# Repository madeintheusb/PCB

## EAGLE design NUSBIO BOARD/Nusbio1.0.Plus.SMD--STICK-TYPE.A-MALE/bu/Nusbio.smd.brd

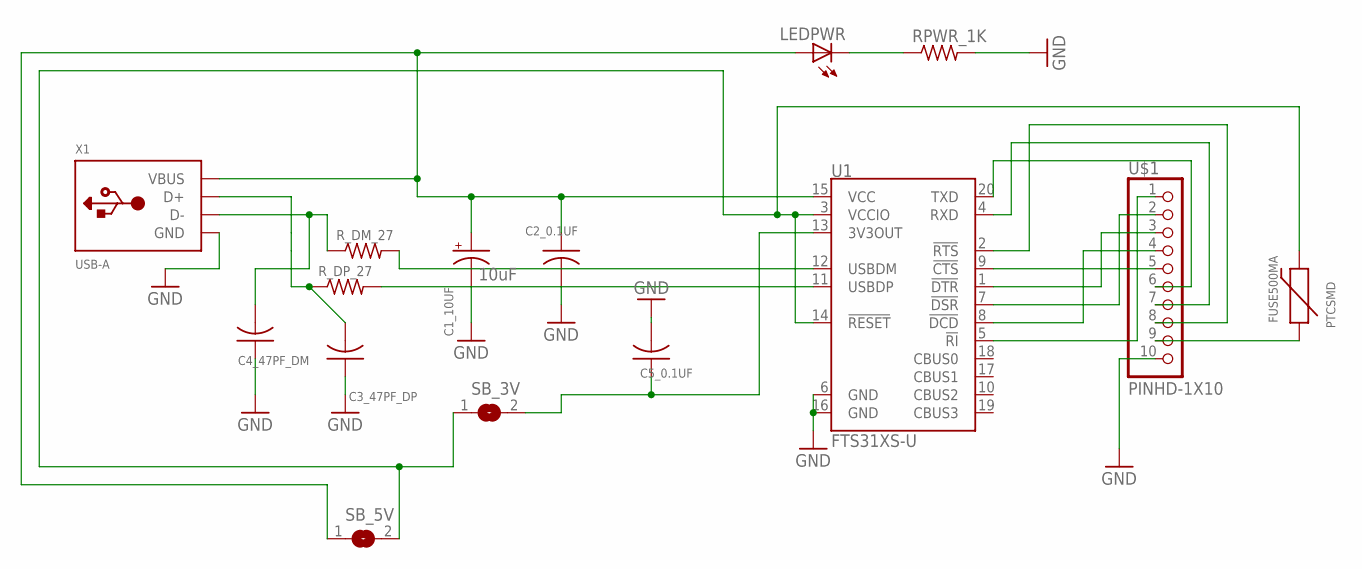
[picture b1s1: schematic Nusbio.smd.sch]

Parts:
C1_10UF: 10uF; EIA3216
C2_0.1UF, C3_47PF_DP, C4_47PF_DM, C5_0.1UF: C-USC1206; C1206
FUSE500MA: PTCSMD; PTC-1206
LEDPWR: LEDCHIPLED_0805; CHIPLED_0805
RPWR_1K: R-US_R0805; R0805
R_DM_27: R-US_R0805; R0805
R_DP_27: R-US_R0805; R0805
SB_3V, SB_5V: SOLDERJUMPERREFLOW; SOLDERJUMPER_REFLOW
U1: FTS31XS-U; SSOP20_L
U$1: PINHD-1X10; 1X10-BIG
X1: USB-A; MOLEX_480371000

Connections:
GND: C1_10UF.C (-), C2_0.1UF.2, C3_47PF_DP.1, C4_47PF_DM.1, C5_0.1UF.2, RPWR_1K.2, U1.6 (GND), U1.16 (GND), U$1.10, X1.4 (GND)
unnamed: FUSE500MA.1, U$1.9
unnamed: C5_0.1UF.1, SB_3V.2, U1.13 (3V3OUT)
unnamed: LEDPWR.C, RPWR_1K.1
unnamed: R_DM_27.2, U1.12 (USBDM)
unnamed: R_DP_27.2, U1.11 (USBDP)
unnamed: U1.20 (TXD), U$1.6
unnamed: U1.7 (!DSR), U$1.2
unnamed: U1.5 (!RI), U$1.1
unnamed: U1.1 (!DTR), U$1.3
unnamed: U1.8 (!DCD), U$1.4
unnamed: U1.9 (!CTS), U$1.5
unnamed: U1.4 (RXD), U$1.7
unnamed: U1.2 (!RTS), U$1.8
unnamed: FUSE500MA.2, SB_3V.1, SB_5V.2, U1.3 (VCCIO), U1.14 (!RESET)
unnamed: C3_47PF_DP.2, R_DP_27.1, X1.3 (D+)
unnamed: C4_47PF_DM.2, R_DM_27.1, X1.2 (D-)
unnamed: C1_10UF.A (+), C2_0.1UF.1, LEDPWR.A, SB_5V.1, U1.15 (VCC), X1.1 (VBUS)

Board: 2 copper layers, 15 parts (0 on the bottom side), 18 nets, no tracks yet.

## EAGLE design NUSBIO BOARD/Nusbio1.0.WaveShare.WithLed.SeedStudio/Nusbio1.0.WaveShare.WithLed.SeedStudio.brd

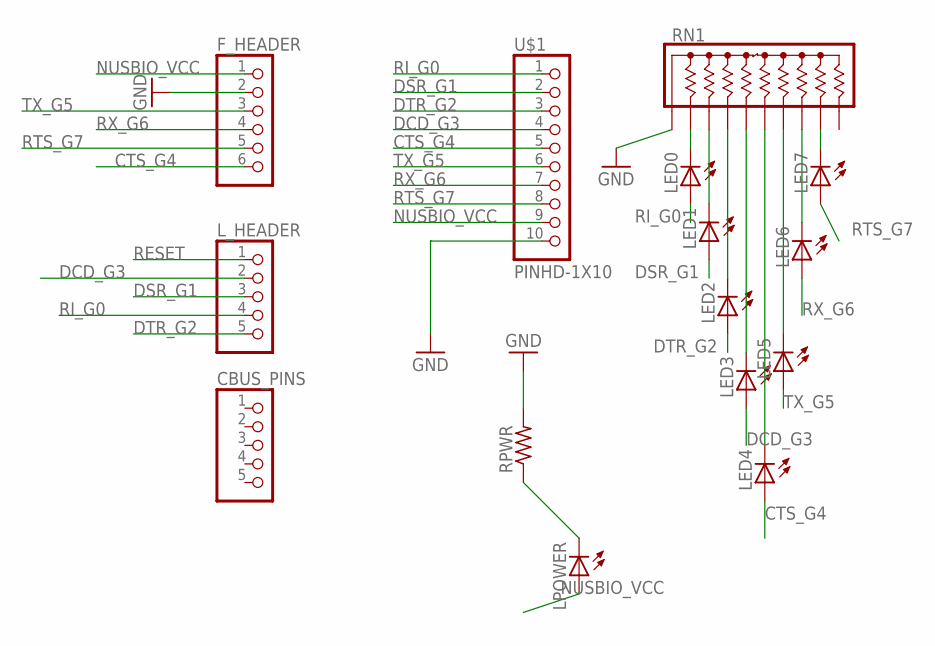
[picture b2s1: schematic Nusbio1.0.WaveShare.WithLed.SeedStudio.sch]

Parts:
CBUS_PINS: PINHD-1X5; 1X05
F_HEADER: PINHD-1X6; 1X06
LED0, LED1, LED2, LED3, LED4, LED5, LED6, LED7: LEDSMT1206; 1206
LPOWER: LEDSMT1206; 1206
L_HEADER: PINHD-1X5; 1X05
RN1: 4610X; SIP10
RPWR: R-US_R1206; R1206
U$1: PINHD-1X10; 1X10-BIG

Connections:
CTS_G4: F_HEADER.6, LED4.A, U$1.5
DCD_G3: LED3.A, L_HEADER.2, U$1.4
DSR_G1: LED1.A, L_HEADER.3, U$1.2
DTR_G2: LED2.A, L_HEADER.5, U$1.3
GND: F_HEADER.2, RN1.1, RPWR.2, U$1.10; also elsewhere on the board
unnamed: LED1.C, RN1.3
unnamed: LED0.C, RN1.2
unnamed: LED2.C, RN1.4
unnamed: LED3.C, RN1.5
unnamed: LED4.C, RN1.6
unnamed: LED7.C, RN1.9
unnamed: LED5.C, RN1.7
unnamed: LED6.C, RN1.8
unnamed 13: LPOWER.C, RPWR.1; also elsewhere on the board
NUSBIO_VCC: F_HEADER.1, LPOWER.A, U$1.9
RESET: L_HEADER.1
RI_G0: LED0.A, L_HEADER.4, U$1.1
RTS_G7: F_HEADER.5, LED7.A, U$1.8
RX_G6: F_HEADER.4, LED6.A, U$1.7
TX_G5: F_HEADER.3, LED5.A, U$1.6

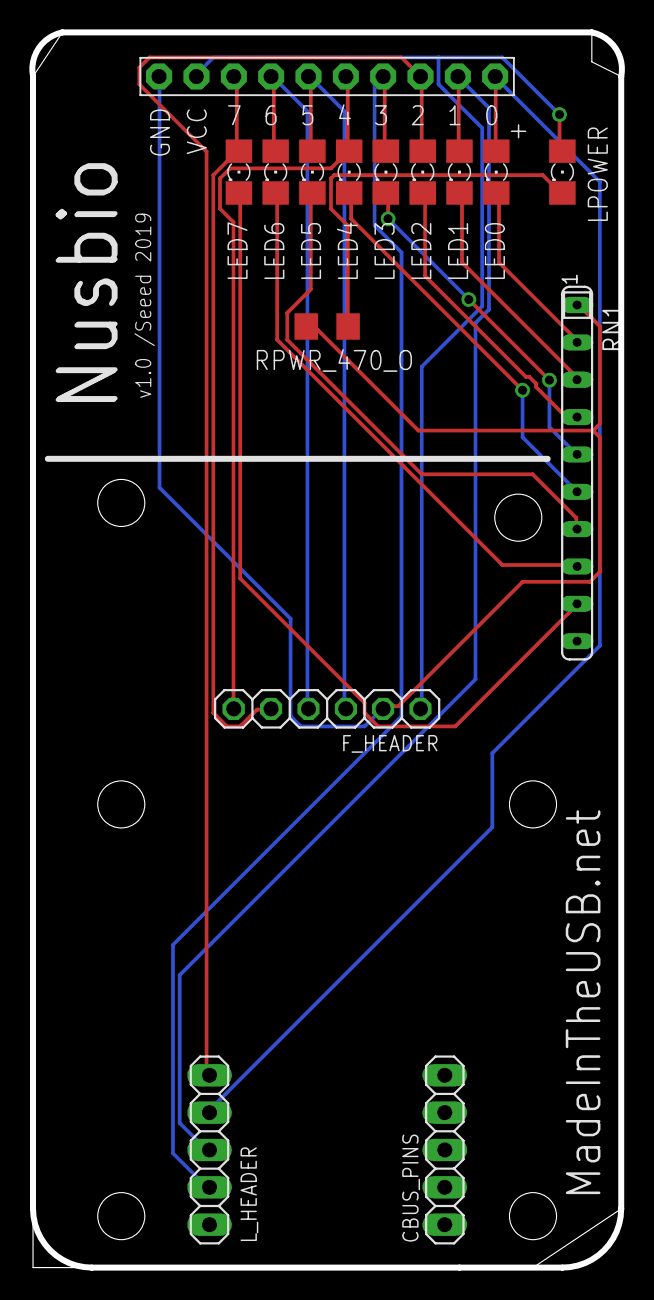
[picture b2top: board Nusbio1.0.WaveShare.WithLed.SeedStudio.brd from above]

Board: 2 copper layers, 40.1 x 84.0 mm, 15 parts (0 on the bottom side), 19 nets.

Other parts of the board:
RPWR_470_O: R1206

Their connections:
GND: RPWR_470_O.2; also elsewhere on the board
unnamed 13: RPWR_470_O.1; also elsewhere on the board

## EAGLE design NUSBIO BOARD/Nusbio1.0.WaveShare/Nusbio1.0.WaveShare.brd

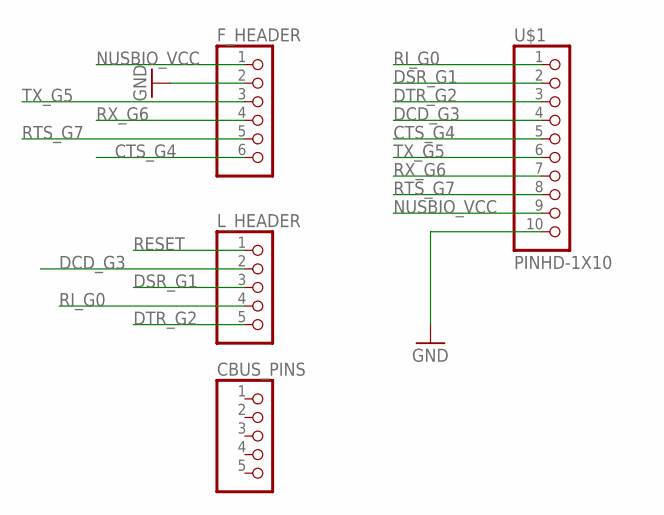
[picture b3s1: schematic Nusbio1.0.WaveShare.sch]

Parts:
CBUS_PINS: PINHD-1X5; 1X05
F_HEADER: PINHD-1X6; 1X06
L_HEADER: PINHD-1X5; 1X05
U$1: PINHD-1X10; 1X10-BIG

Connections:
CTS_G4: F_HEADER.6, U$1.5
DCD_G3: L_HEADER.2, U$1.4
DSR_G1: L_HEADER.3, U$1.2
DTR_G2: L_HEADER.5, U$1.3
GND: F_HEADER.2, U$1.10
NUSBIO_VCC: F_HEADER.1, U$1.9
RESET: L_HEADER.1
RI_G0: L_HEADER.4, U$1.1
RTS_G7: F_HEADER.5, U$1.8
RX_G6: F_HEADER.4, U$1.7
TX_G5: F_HEADER.3, U$1.6

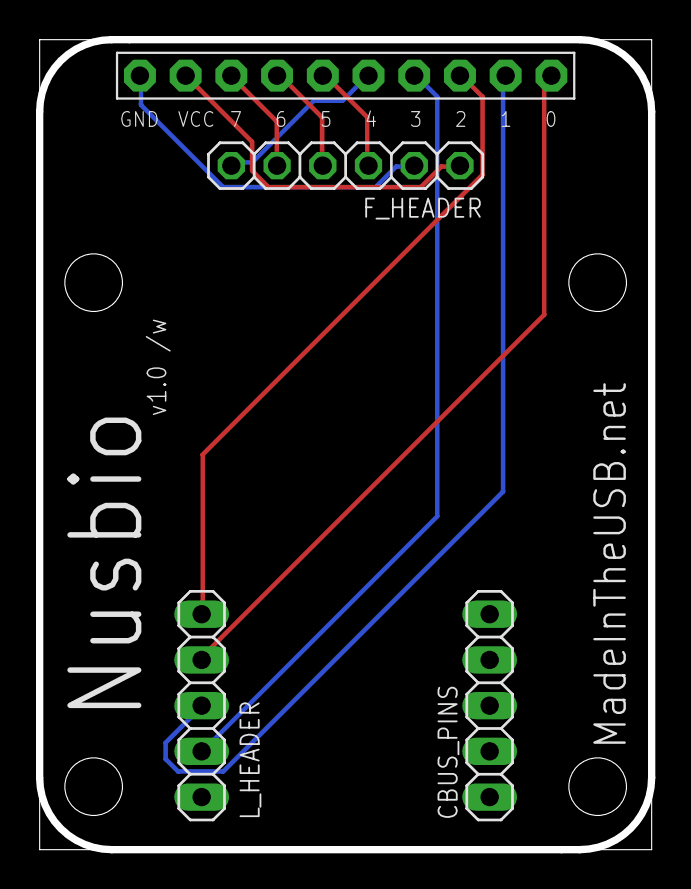
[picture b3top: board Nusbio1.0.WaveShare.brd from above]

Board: 2 copper layers, 34.0 x 45.0 mm, 4 parts (0 on the bottom side), 10 nets.

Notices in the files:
parts and their libraries:
SparkFun-Capacitors: Licensing: Creative Commons ShareAlike 4.0 International - https://creativecommons.org/licenses/by-sa/4.0
microbuilder: This work is placed in the public domain, and may be freely used for commercial and non-commercial work with the following conditions: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
